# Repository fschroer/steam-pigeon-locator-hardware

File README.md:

# Steam Pigeon locator hardware

KiCad 10 design for the Steam Pigeon rocket locator: an STM32WL5MOC LoRa module with GPS, IMU, barometer, flash, USB-C charging and four deployment channels. Firmware lives in [steam-pigeon-locator](https://github.com/fschroer/steam-pigeon-locator).

## Board at a glance

| Block | Parts |
| --- | --- |
| MCU and radio | STM32WL5MOCH6TR (U5), U.FL antenna (J7), high-power PA configuration |
| GPS | u-blox SAM-M10Q (U2), I2C2 at 0x42 |
| Sensors | ISM6HG256X IMU (U14), MS5611 barometer (U16), MX25L6436F flash (U17), all on SPI2 |
| Power | BQ25185 charger (U18), RT9080-33 LDO (U7), DRV5032 Hall sensor and 74HCS00 latch for magnet on/off |
| USB | USB-C (J1), CH340N serial (U4) |
| Deployment | Arm switch U13 (DMP2021UFDF) driven by DARM, four TPS22950 high-side switches plus PMXB43UNE (DFN1010D-3) low-side return switches (Q4-Q7) on J2 and J4; continuity sense DS1-DS4 on the return side |
| Audio | PAM8904 piezo driver (U11) |

Board size is 54 x 25 mm, 4 layers. The silkscreen carries the board revision (currently `SPL915STM B01`).

## Repository layout

| Path | Contents |
| --- | --- |
| `RocketLocator.kicad_pro`, `.kicad_sch`, `.kicad_pcb` | The design |
| `lib/` | Project-local symbol and footprint libraries |
| `sym-lib-table`, `fp-lib-table` | Project library tables pointing into `lib/` |
| `BOM/RocketLocatorBOM.xlsx` | Purchasing BOM: JLCPCB part numbers, cost, stock and order tracking, plus a JLCPCB upload sheet. Maintained by hand; keep it in step with the schematic |
| `.github/workflows/kicad.yml` | ERC, DRC and fab outputs on every push |

Generated files (Gerbers, drill, BOM, CPL, netlist, PDF) are not committed. CI builds them on every push as a downloadable workflow artifact, and attaches them to a GitHub release when you push a board tag.

## Open design issues

Findings from the 2026-10-15 design review are tracked as GitHub issues. The full write-up is in the [RocketLocator design review](https://claude.ai/code/artifact/725ce922-3286-4f00-98c2-284a111a1c0e).

## Libraries

Non-stock parts live in `lib/` and are registered in the project's `sym-lib-table` and `fp-lib-table` with `${KIPRJMOD}` paths, so a fresh clone opens without any global library setup. Project entries override a global library with the same nickname.

| Library | Contents | Source |
| --- | --- | --- |
| `Custom.kicad_sym`, `Custom.pretty` | Project symbols and footprints | Copied from the personal KiCad 9.0 `Custom` libraries, 2026-10-15 |
| `RT9080-33GJ5.kicad_sym` | RT9080-33 LDO symbol | Extracted from the schematic's embedded symbol cache |
| `STM32WL5MOCH6TR.kicad_sym` | STM32WL5MOC module symbol | Extracted from the schematic's embedded symbol cache |
| `U.FL-R-SMT_01_.kicad_sym` | U.FL receptacle symbol | Extracted from the schematic's embedded symbol cache |

`Custom.pretty` also holds `SOT94P280X100-5N` (U7) and `SOP-8_5.28x5.23mm_P1.27mm` (U17). Their original libraries (`RT9080`, `Package_SO_New`) no longer existed, so they were recovered from the board file, converted back to front-side library form, and the design was relinked to `Custom:`.

When you change a part, edit it in `lib/` (not in your personal library) and commit it with the design change. 3D models live in `lib/3dmodels` (see its README) and are referenced with `${KIPRJMOD}` paths, so **File > Export > STEP** and CI's `fab/RocketLocator.step` include every part. When you add a footprint, give it a model there too (copy a stock STEP into `lib/3dmodels/kicad/`, or add a generator entry in `tools/gen_3dmodels.py`), then add it to `tools/set_3dmodels.py`.

## Releasing a board

1. Make sure ERC and DRC are clean.
2. Update the silkscreen revision and date.
3. Commit, then tag with the board revision and order date, for example `git tag B02-2026-11-20 && git push --tags`.
4. Download the Gerber zip, BOM, CPL and STEP from the release and upload them to the fab.

## Working copy

Keep the working copy outside Google Drive, OneDrive or Dropbox, because folder sync corrupts the `.git` directory. GitHub is the backup.

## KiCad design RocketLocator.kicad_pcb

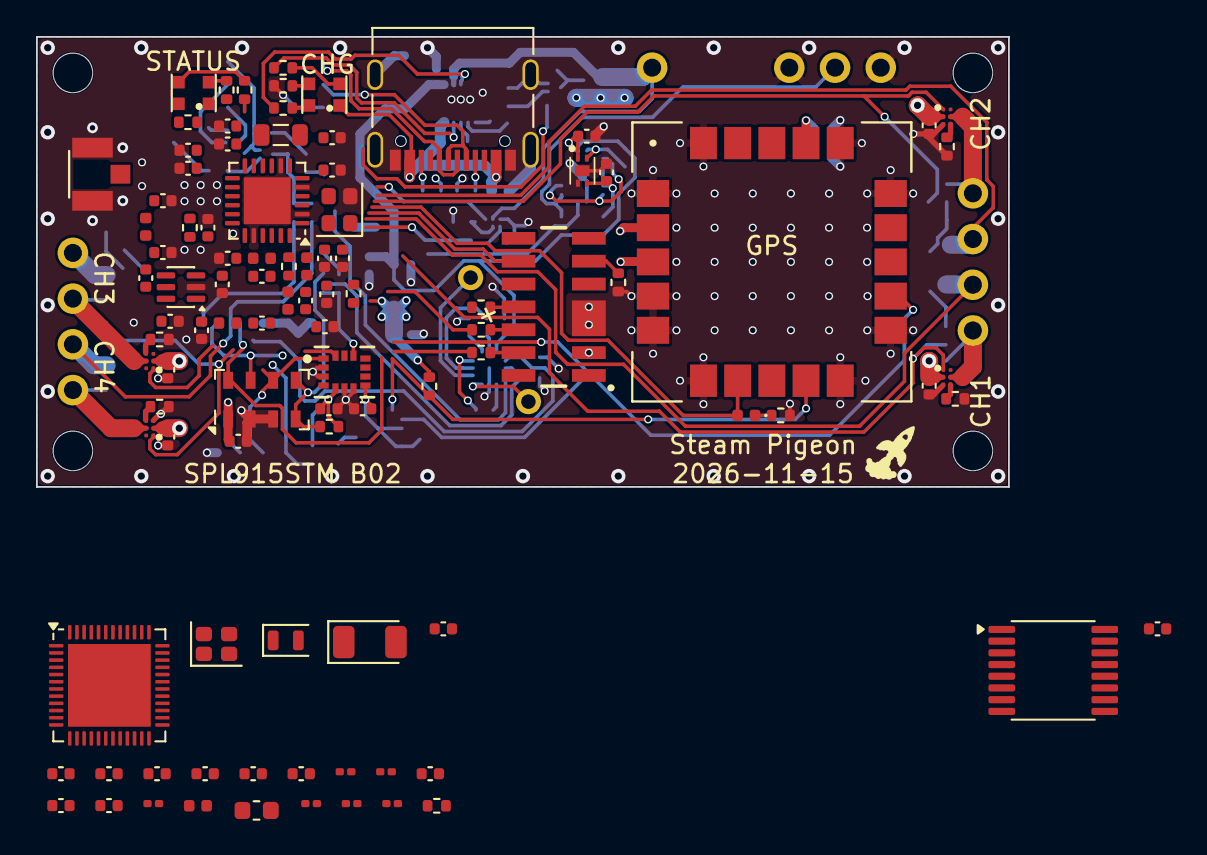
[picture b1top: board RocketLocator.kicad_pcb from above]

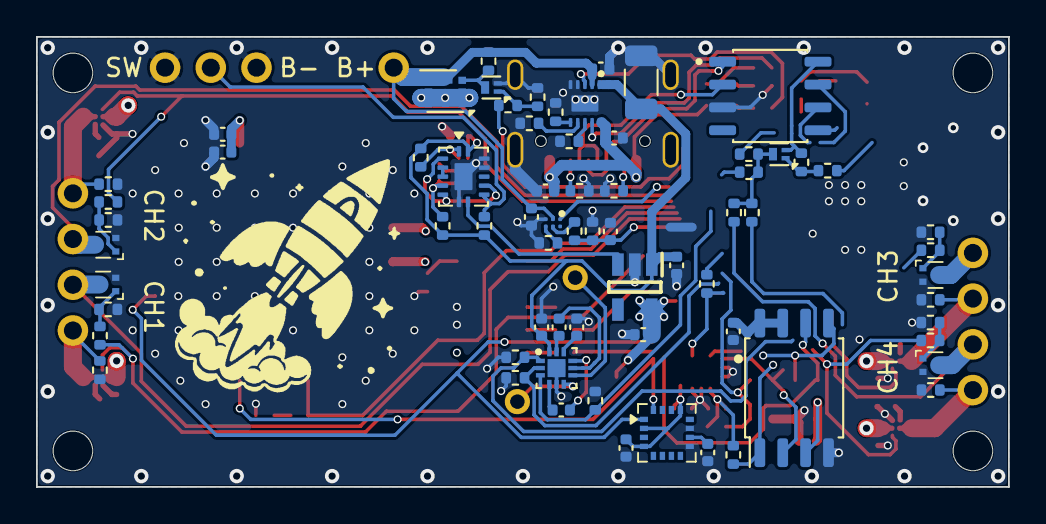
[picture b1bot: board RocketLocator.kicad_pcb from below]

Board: 4 copper layers, 54.0 x 25.0 mm, 177 parts (70 on the bottom side), 124 nets.

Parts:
AE1: 2450AT18D0100002E; Johanson_2450AT18x100
C1, C6, C7, C8, C9, C10, C20, C36: 0.1uF; C_0402_1005Metric
C2, C3, C4, C5, C11, C12, C13, C14, C18, C38: 1uF; C_0402_1005Metric
C15, C16, C21, C45, C70: 2.2uF; C_0402_1005Metric
C17, C44, C53: 10nF; C_0402_1005Metric
C19, C51: 4.7uF; C_0402_1005Metric
C26: 47uF; C_1206_3216Metric
C32, C37, C39: 10uF; C_0402_1005Metric
C40, C41, C42, C43, C48, C49, C50, C61, C63: 100nF; C_0402_1005Metric
C46: 1.5pF; C_0201_0603Metric
C47: 2.0pF; C_0201_0603Metric
C52: 470nF; C_0402_1005Metric
C54: 47nF; C_0402_1005Metric
C55: 47pF; C_0402_1005Metric
C56: 3.0pF; C_0402_1005Metric
C57: 5.6pF; C_0402_1005Metric
C58, C62: 39pF; C_0402_1005Metric
C59, C66: DNP; C_0402_1005Metric
C60: 2.4pF; C_0402_1005Metric
C64, C65: 1.8pF; C_0402_1005Metric
C67: 1nF; C_0402_1005Metric
C68, C69: 3.3pF; C_0402_1005Metric
C71: 2.2nF; C_0402_1005Metric
C72: 3.9pF; C_0402_1005Metric
C73: 0.3pF; C_0201_0603Metric
D1: Green LED; LED_0402_1005Metric
D4, D5: LED_XL-Z1912RGBA-SG
FB1: 120R@100MHz; L_0402_1005Metric
G1: SteamPigeon_Logo_13mm
G2: SteamPigeon_Logo_3mm
H1, H2, H3, H4: MountingHole; MountingHole_2.2mm_M2
J1: USB_C; USB_C_Receptacle_Palconn_UTC16-G
J2: Deploy Ch1 / Ch2; PinHeader_1x04_P2.54mm_Vertical
J4: Deploy Ch3 / Ch4; PinHeader_1x04_P2.54mm_Vertical
J7: U.FL-R-SMT(01); HRS_U.FL-R-SMT(01)
J8: Conn_ST_STDC14; SAMTEC_FTR-107-51-G-D
J12: Battery / Switch; PinHeader_1x06_P2.54mm_Vertical_Pos4-5_Empty
L1: 4.7uH; L_0603_1608Metric
L2: 2.7nH; L_0201_0603Metric
L3, L4: 3.5nH; L_0201_0603Metric
L5: 15uH; L_0805_2012Metric
L6: 47nH; L_0402_1005Metric
L8: 2.5nH; L_0402_1005Metric
L9: 15nH; L_0402_1005Metric
L10: 4.7nH; L_0402_1005Metric
L11: 9.1nH; L_0402_1005Metric
LS1: SPKR; PiezoBuzzer
Q1: 2N7002KN; DFN1006-3L
Q3: BSS84; DFN1006-3L
Q4, Q5, Q6, Q7: PMXB43UNE; Nexperia_DFN1010D-3_SOT1215
R1, R23, R26, R31, R40, R41: 10K; R_0402_1005Metric
R2, R18, R24, R36, R38: 620; R_0402_1005Metric
R3, R17, R30: 1M; R_0402_1005Metric
R4, R35, R43, R45, R46, R47, R48, R57: 100; R_0402_1005Metric
R5, R13, R14: 47; R_0402_1005Metric
R6: 218; R_0402_1005Metric
R7: 375; R_0402_1005Metric
R8: 13K; R_0402_1005Metric
R9: 8.2K; R_0402_1005Metric
R10, R25: 5.1K; R_0402_1005Metric
R11: 27K; R_0402_1005Metric
R15: 35; R_0402_1005Metric
R16: 109; R_0402_1005Metric
R19: 98; R_0402_1005Metric
R20, R29, R42, R44, R49, R50, R51, R52: 100K; R_0402_1005Metric
R21, R22: 4.7K; R_0402_1005Metric
R27, R28, R37, R39: 47K; R_0402_1005Metric
R32: 470; R_0402_1005Metric
R33, R34: 120; R_0402_1005Metric
R53, R54, R55, R56: 1K; R_0402_1005Metric
R58: 0R; R_0402_1005Metric
R59: 1k; R_0402_1005Metric
U1, U6, U8, U9, U15: TPS22950YBHR; IC_TPS22950YBHR
U2: SAM-M10Q-00B; XCVR_SAM-M10Q-00B
U3: DRV5032DUDMRR; X2SON
U4: CH340N; JEITA_SOIC-8_3.9x4.9mm_P1.27mm
U7: RT9080-33GJ5; SOT94P280X100-5N
U11: PAM8904EGPR; W-QFN2020-12-EP(2x2)
U12: 74HCS00; WQFN 14 3.00 mm × 2.50 mm
U13: DMP2021UFDF; Diodes_UDFN2020-6_Type-F
U14: ISM6HG256XTR; U_LGA-14L_2p5X3p0X0p83_STM
U16: MS5611-01BA; LGA-8_3x5mm_P1.25mm
U17: MX25L6436F; SOP-8_5.28x5.23mm_P1.27mm
U18: BQ25185DLHR
U19: MMC5983MA; LGA-16_3x3mm_P0.5mm
U20: nRF54L15-QFAA; QFN-48-1EP_6x6mm_P0.4mm_EP4.6x4.6mm
U21: SX1262IMLTRT; QFN-24-1EP_4x4mm_P0.5mm_EP2.6x2.6mm
U22: TCA9534PWR; TSSOP-16_4.4x5mm_P0.65mm
U23: PE4259; SOT-363_SC-70-6
Y1: 32MHz CL8pF; Crystal_SMD_2016-4Pin_2.0x1.6mm
Y2: 32.768kHz CL7pF; Crystal_SMD_2012-2Pin_2.0x1.2mm
Y3: 32MHz TCXO; Oscillator_SMD_SiT_PQFN-4Pin_2.0x1.6mm

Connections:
3V3SW: Q3.3 (D), R27.1, R28.2, R37.1, R39.2
$NRST: J8.12 (~RST), R59.1
$SCL: R22.2, U2.12 (SCL), U19.1 (SCL/SPI_SCK), U20.42, U22.14
$SDA: R21.2, U2.9 (SDA), U19.16 (SDA/SPI_SDI), U20.41, U22.15
$SWCLK: R5.1, U20.26
$SWDIO: C72.1, R13.1, U20.25
$VCP_RX: U4.6 (TXD), U20.24
$VCP_TX: U4.7 (RXD), U20.23
+3V3: C1.1, C8.2, C9.1, C10.1, C19.1, C32.1, C36.2, C38.1, C39.1, C40.1, C41.1, C42.1, C43.1, C48.1, C49.1, C50.1, C51.1, C61.1, C63.1, D5.1, J8.3 (VCC), Q3.2 (S), R1.2, R21.1, R22.1, R23.2, R26.2, R40.2, U2.2 (V_IO), U2.3 (V_BCKP), U2.17 (VCC), U4.5 (VCC), U4.8 (V3), U7.5 (VOUT), U14.5 (VDDIO), U14.8 (VDD), U16.1 (VDD), U17.3 (~WP), U17.7 (~HOLD), U17.8 (VCC), U19.2 (VDD), U19.4 (~SPI_CS), U19.13 (VDDIO), U20.10, U20.22, U20.36, U20.47, U20.48, U21.1, U21.10, U21.11, U22.16, U23.6
+5V: C11.1, C20.1, D4.1, J1.A4 (VBUS), J1.A9 (VBUS), J1.B4 (VBUS), J1.B9 (VBUS), U18.10 (IN)
+BATT: C12.2, C18.2, J12.4, R20.1, U8.B1 (VIN), U13.4 (S), U13.8 (S), U18.2 (BAT)
/MCU_Radio/DCC: L1.1, U20.46
/MCU_Radio/DECA: C44.1, C70.1, C71.1, FB1.2, U20.33, U20.43
/MCU_Radio/DECD: C45.1, FB1.1, L1.2, U20.45
/MCU_Radio/LORA_BUSY: U20.19, U21.14
/MCU_Radio/LORA_DCC: L5.1, U21.9
/MCU_Radio/LORA_DIO1: U20.20, U21.13
/MCU_Radio/LORA_NRESET: U20.18, U21.15
/MCU_Radio/LORA_NSS: U20.17, U21.19
/MCU_Radio/LORA_RFI_N: C60.1, L9.1, U21.22
/MCU_Radio/LORA_RFI_P: C64.1, L9.2, U21.21
/MCU_Radio/LORA_RFO: R58.1, U21.23
/MCU_Radio/LORA_TX1: C56.2, C57.1, C58.1, L8.2
/MCU_Radio/LORA_TX2: C58.2, L10.1
/MCU_Radio/LORA_TXA: C56.1, C59.1, L6.2, L8.1, R58.2
/MCU_Radio/LORA_VREG: C52.1, L5.2, U21.7
/MCU_Radio/LORA_VR_PA: C54.1, C55.1, L6.1, U21.24
/MCU_Radio/NRF_ANT: L2.1, U20.31
/MCU_Radio/NRF_NRESET: R59.2, U20.30
/MCU_Radio/NRF_RF1: C46.1, L2.2, L3.1
/MCU_Radio/NRF_RF2: C47.1, L3.2, L4.1
/MCU_Radio/NRF_RF3: AE1.1, C73.1, L4.2
/MCU_Radio/RF_ANT1: C62.2, C68.1, L11.1
/MCU_Radio/RF_COM: C62.1, U23.5
/MCU_Radio/RF_RX: C60.2, C66.1, U23.3
/MCU_Radio/RF_SW_CTRL: R57.1, U21.12
/MCU_Radio/RF_SW_CTRL_F: C67.1, R57.2, U23.4
/MCU_Radio/RF_TX: C65.1, L10.2, U23.1
/MCU_Radio/TCXO_OUT: U21.3, Y3.3
/MCU_Radio/TCXO_VCC: C53.1, U21.6, Y3.4
/MCU_Radio/XC1: U20.34, Y1.1
/MCU_Radio/XC2: U20.35, Y1.3
/MCU_Radio/XL1: U20.1, Y2.1
/MCU_Radio/XL2: U20.2, Y2.2
BATTLVL: C7.1, R9.1, R11.1, U20.5
BATTRD: U8.A1 (ON), U22.9
CSB_ALT: R23.1, U16.4 (CSB), U16.5 (CSB), U20.14
CSB_MEM: R1.1, U17.1 (~CS), U20.16
CS_IMU: R26.1, U14.12 (CS), U20.11
D1: R45.2, U15.A1 (ON), U20.27
D2: R46.2, U6.A1 (ON), U20.28
D3: R47.2, U1.A1 (ON), U20.29
D4: R48.2, U9.A1 (ON), U20.6
DARM: R35.1, U20.40
DEPLOY1+: J2.1, R53.1, U15.B2 (VOUT)
DEPLOY2+: J2.4, R54.1, U6.B2 (VOUT)
DEPLOY3+: J4.2, R55.1, U1.B2 (VOUT)
DEPLOY4+: J4.4, R56.1, U9.B2 (VOUT)
DPWR: C2.2, C3.2, C4.2, C5.2, U1.B1 (VIN), U6.B1 (VIN), U9.B1 (VIN), U13.1 (D), U13.2 (D), U13.5 (D), U13.6 (D), U13.7 (D), U15.B1 (VIN)
DS1: J2.2, Q4.3 (D), R27.2, U20.7
DS2: J2.3, Q5.3 (D), R28.1, U20.8
DS3: J4.1, Q6.3 (D), R37.2, U20.9
DS4: J4.3, Q7.3 (D), R39.1, U20.37
DSON: R43.1, U22.7
EN1: R29.2, U11.1 (EN1), U20.38
EN2: R44.2, U11.2 (EIN2), U20.39
GND: C1.2, C2.1, C3.1, C4.1, C5.1, C6.2, C7.2, C8.1, C9.2, C10.2, C11.2, C12.1, C15.1, C16.1, C17.1, C18.1, C19.2, C20.2, C21.1, C26.1, C32.2, C36.1, C37.2, C38.2, C39.2, C40.2, C41.2, C42.2, C43.2, C44.2, C45.2, C46.2, C47.2, C48.2, C49.2, C50.2, C51.2, C52.2, C53.2, C54.2, C55.2, C57.2, C59.2, C61.2, C63.2, C64.2, C65.2, C66.2, C67.2, C68.2, C69.2, C70.2, C71.2, C72.2, C73.2, J1.A1 (GND), J1.A12 (GND), J1.B1 (GND), J1.B12 (GND), J1.S1 (SHIELD), J7.1 (GND), J7.2 (GND), J8.5 (GND), J8.7 (GND), J12.1, J12.3, Q1.2 (S), Q4.2 (S), Q5.2 (S), Q6.2 (S), Q7.2 (S), R2.1, R4.2, R7.1, R8.1, R10.2, R11.2, R18.1, R24.1, R25.2, R29.1, R31.1, R32.1, R34.1, R36.1, R38.1, R41.2, R42.1, R44.1, R49.2, R50.2, R51.2, R52.2, R53.2, R54.2, R55.2, R56.2, U1.C1 (GND), U2.1 (GND), U2.4 (GND), U2.5 (GND), U2.6 (GND), U2.10 (GND), U2.11 (GND), U2.15 (GND), U2.16 (GND), U2.20 (GND), U3.2 (GND), U3.5 (PAD), U4.3 (GND), U6.C1 (GND), U7.2 (GND), U8.C1 (GND), U9.C1 (GND), U11.5 (GND), U11.13 (TP), U12.7 (GND), U12.12, U12.13, U12.15 (TP), U14.2 (SDX), U14.3 (SCX), U14.6 (GND), U14.7 (GND), U15.C1 (GND), U16.2 (PS), U16.3 (GND), U17.4 (GND), U18.4 (~CE), U18.5 (GND), U18.11 (TP), U19.9 (GND), U19.11 (GND), U20.32, U20.44, U20.49, U21.2, U21.5, U21.8, U21.20, U21.25, U22.1, U22.2, U22.3, U22.8, U23.2, Y1.2, Y1.4, Y3.2
MSW: J12.2, R17.2, U12.9
unnamed: D1.1 (K), R34.2
unnamed: D4.2, R6.2
unnamed: D4.3, R7.2
unnamed: D4.4, R33.2
unnamed: D5.2, R19.2
unnamed: D5.3, R16.2
unnamed: D5.4, R15.2
unnamed: J1.A5 (CC1), R10.1
unnamed: J1.B5 (CC2), R25.1
unnamed: J8.11 (GNDDetect), R4.1
unnamed: J8.6 (JCLK/SWCLK), R5.2
unnamed: J8.8 (JTDO/SWO), R14.2
unnamed: J8.4 (JTMS/SWDIO), R13.2
unnamed: Q1.3 (D), R20.2, U13.3 (G)
unnamed: Q1.1 (G), R35.2, R41.1
unnamed: Q3.1 (G), R40.1, R43.2
unnamed: Q4.1 (G), R45.1, R49.1
unnamed: Q5.1 (G), R46.1, R50.1
unnamed: Q6.1 (G), R47.1, R51.1
unnamed: Q7.1 (G), R48.1, R52.1
unnamed: R24.2, U1.C2 (ILIM)
unnamed: R30.2, U3.4 (OUT1), U12.1
unnamed: C17.2, R3.2, U3.3 (OUT2), U12.5
unnamed: J1.A6 (D+), J1.B6 (D+), U4.1 (UD+)
unnamed: J1.A7 (D-), J1.B7 (D-), U4.2 (UD-)
unnamed: R36.2, U6.C2 (ILIM)
unnamed: U7.3 (EN), U12.8
unnamed: R2.2, U8.C2 (ILIM)
unnamed: R9.2, U8.B2 (VOUT)
unnamed: R38.2, U9.C2 (ILIM)
unnamed: C13.1, U11.4 (CN1)
unnamed: C14.1, U11.8 (CN2)
unnamed: C13.2, U11.9 (CP1)
unnamed: C14.2, U11.11 (CP2)
unnamed: LS1.1, U11.7 (VO1)
unnamed: LS1.2, U11.6 (VO2)
unnamed: C15.2, U11.10 (VOUT)
unnamed: U12.3, U12.4
unnamed: U12.2, U12.6, U12.10
unnamed: R18.2, U15.C2 (ILIM)
unnamed: R8.2, U18.7 (ILIM/VSET)
unnamed: R32.2, U18.8 (ISET)
unnamed: R31.2, U18.6 (TS/MR)
unnamed: C37.1, U19.10 (CAP)
RF_LORA: C69.1, J7.3 (SIG), L11.2
SCLK: U14.13 (SCL), U16.8 (SCLK), U17.6 (SCLK), U20.12, U21.18
SDI: U14.14 (SDA), U16.7 (SDI/SDA), U17.5 (SI/SIO0), U20.13, U21.17
SDO: U14.1 (SDO/TA0), U16.6 (SDO), U17.2 (SO/SIO1), U20.15, U21.16
SOFT_LED1: R19.1, U22.4
SOFT_LED2: R16.1, U22.5
SOFT_LED3: R15.1, U22.6
SPKR: R42.2, U11.3 (DIN), U20.4
STAT1: R6.1, U18.9 (STAT1)
STAT2: R33.1, U18.3 (STAT2)
SYS: C6.1, C16.2, C21.2, C26.2, R3.1, R17.1, R30.1, U3.1 (VCC), U7.1 (VIN), U11.12 (VIN), U12.14 (VCC), U18.1 (SYS)
TIMEPULSE: D1.2 (A), U2.7 (TIMEPULSE), U20.3

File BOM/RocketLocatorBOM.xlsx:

Comment | Designator | Footprint | JLCPCB Part #（optional）
2.2uF | C15,C16,C21,C45,C70 | C_0402_1005Metric | C307418
10nF | C17,C44,C53 | C_0402_1005Metric | C15195
10uF | C32,C37,C39 | C_0402_1005Metric | C15525
1uF | C2,C3,C4,C5,C11,C12,C13,C14,C18,C38 | C_0402_1005Metric | C52923
0.1uF | C1,C6,C7,C8,C9,C10,C20,C36,C40,C41,C42,C43,C48,C49,C50,C61,C63 | C_0402_1005Metric | C1525
47uF | C26 | C_1206_3216Metric | C96123
4.7uF | C19,C51 | C_0402_1005Metric | C368809
Green LED | D1 | LED_0402_1005Metric | C965794
LED_XL-Z1912RGBA-SG | D4,D5 | LED_XL-Z1912RGBA-SG | C22461785
USB_C | J1 | USB_C_Receptacle_Palconn_UTC16-G | C2927038
U.FL-R-SMT(01) | J7 | HRS_U.FL-R-SMT(01) | C5137195
2N7002KN | Q1 | DFN1006-3L | C49009905
BSS84 | Q3 | DFN1006-3L | C42394022
PMXB43UNE | Q4,Q5,Q6,Q7 | Nexperia_DFN1010D-3_SOT1215 | C547273
5.1K | R10,R25 | R_0402_1005Metric | C294638
27K 0.1% | R11 | R_0402_1005Metric | C25207446
33 | R15 | R_0402_1005Metric | C25105
620 | R2,R18,R24,R36,R38 | R_0402_1005Metric | C4961
1M | R3,R17,R30 | R_0402_1005Metric | C26083
470 | R32 | R_0402_1005Metric | C25117
120 | R33,R34 | R_0402_1005Metric | C25079
47K | R27,R28,R37,R39 | R_0402_1005Metric | C25792
10K | R1,R23,R26,R31,R40,R41 | R_0402_1005Metric | C25531
4.7K | R21,R22 | R_0402_1005Metric | C25900
100 | R4,R16,R19,R35,R43,R45,R46,R47,R48,R57 | R_0402_1005Metric | C25076
47 | R5,R13,R14 | R_0402_1005Metric | C25118
220 | R6 | R_0402_1005Metric | C25091
374 | R7 | R_0402_1005Metric | C48971914
13K | R8 | R_0402_1005Metric | C25754
8.2K 0.1% | R9 | R_0402_1005Metric | C24265089
100K | R20,R29,R42,R44,R49,R50,R51,R52 | R_0402_1005Metric | C25741
1K | R53,R54,R55,R56,R59 | R_0402_1005Metric | C11702
TPS22950YBHR | U1,U6,U8,U9,U15 | IC_TPS22950YBHR | C3230039
PAM8904EGPR | U11 | W-QFN2020-12-EP(2x2) | C510550
SN74HCS00BQA-Q1 | U12 | WQFN 14 3.00 mm × 2.50 mm | C4469587
DMP2021UFDF | U13 | Diodes_UDFN2020-6_Type-F | C151459
ISM6HG256XTR | U14 | U_LGA-14L_2p5X3p0X0p83_STM | C51931514
MS5611-01BA | U16 | LGA-8_3x5mm_P1.25mm | C15639
MX25L6436F | U17 | SOP-8_5.28x5.23mm_P1.27mm | C2830754
BQ25185DLHR | U18 | BQ25185DLHR | C19725033
SAM-M10Q-00B | U2 | XCVR_SAM-M10Q-00B | C5443880
DRV5032DUDMRR | U3 | X2SON | C2152495
CH340N | U4 | JEITA_SOIC-8_3.9x4.9mm_P1.27mm | C2977777
RT9080-33GJ5 | U7 | SOT94P280X100-5N | C841192
MMC5983MA | U19 | LGA-16_3x3mm_P0.5mm | C404329
1.5pF | C46 | C_0201_0603Metric | C435397
2.0pF | C47 | C_0201_0603Metric | C668326
470nF | C52 | C_0402_1005Metric | C47339
47nF | C54 | C_0402_1005Metric | C126529
47pF | C55 | C_0402_1005Metric | C161322
3.0pF | C56 | C_0402_1005Metric | C88891
5.6pF | C57 | C_0402_1005Metric | C88895
39pF | C58,C62 | C_0402_1005Metric | C426038
2.4pF | C60 | C_0402_1005Metric | C88888
1.8pF | C64,C65 | C_0402_1005Metric | C76902
1nF | C67 | C_0402_1005Metric | C1523
3.3pF | C68,C69 | C_0402_1005Metric | C88892
2.2nF | C71 | C_0402_1005Metric | C1531
3.9pF | C72 | C_0402_1005Metric | C76907
120R@100MHz | FB1 | L_0402_1005Metric | C85812
4.7uH | L1 | L_0603_1608Metric | C114862
2.7nH | L2 | L_0201_0603Metric | C7216765
3.5nH | L3 | L_0201_0603Metric | C3911055
15uH | L5 | L_0805_2012Metric | C486333
47nH | L6 | L_0402_1005Metric | C22334
2.5nH | L8 | L_0402_1005Metric | C703121
15nH | L9 | L_0402_1005Metric | C91621
4.7nH | L10 | L_0402_1005Metric | C167480
9.1nH | L11 | L_0402_1005Metric | C337956
0R | R58 | R_0402_1005Metric | C17168
nRF54L15-QFAA | U20 | QFN-48-1EP_6x6mm_P0.4mm_EP4.6x4.6mm | C42458750
SX1262IMLTRT | U21 | QFN-24-1EP_4x4mm_P0.5mm_EP2.6x2.6mm | C191341
TCA9534PWR | U22 | TSSOP-16_4.4x5mm_P0.65mm | C783615
PE4259 | U23 | SOT-363_SC-70-6 | C470892
32MHz CL8pF | Y1 | Crystal_SMD_2016-4Pin_2.0x1.6mm | C718072
32.768kHz CL7pF | Y2 | Crystal_SMD_2012-2Pin_2.0x1.2mm | C99009
32MHz TCXO | Y3 | Oscillator_SMD_SiT_PQFN-4Pin_2.0x1.6mm | C3007493
